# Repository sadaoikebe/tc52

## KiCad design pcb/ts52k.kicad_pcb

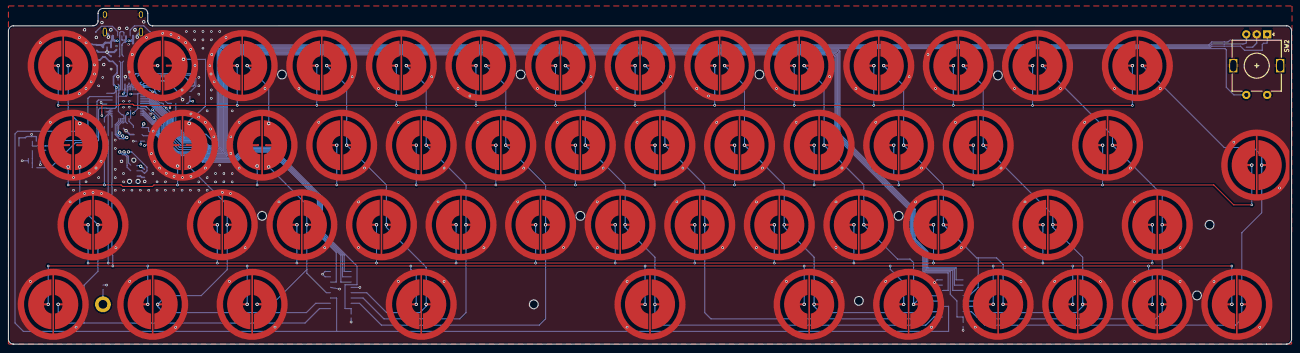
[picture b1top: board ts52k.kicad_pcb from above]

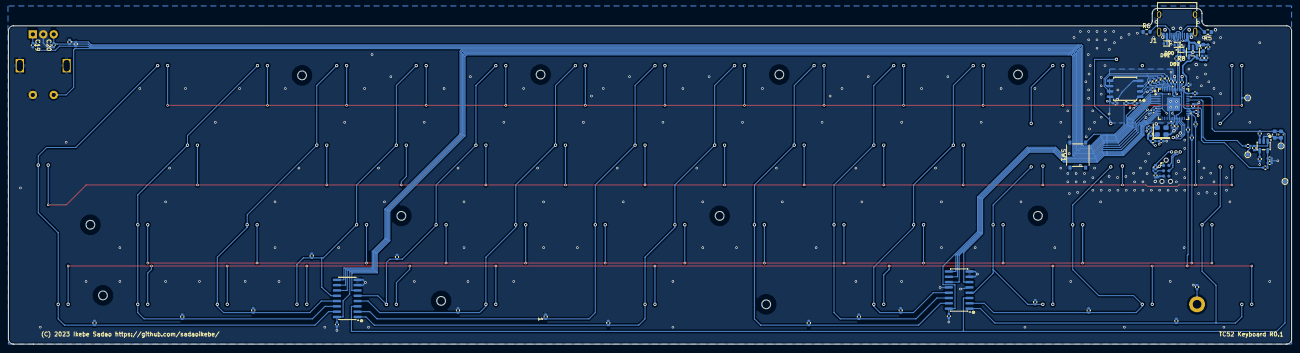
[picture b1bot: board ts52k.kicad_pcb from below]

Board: 4 copper layers, 307.2 x 80.4 mm, 148 parts (83 on the bottom side), 68 nets.

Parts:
C2, C4, C6, C7, C8, C9, C10, C12, C13, C14, C15, C16, C17, C18, C21: 1u; C_0402_1005Metric
C3: 4.7u; C_0603_1608Metric
C5, C32, C37: 4.7u; C_0402_1005Metric
C19, C20, C33, C34, C35: 0.1u; C_0402_1005Metric
C30: 300p C0G; C_0603_1608Metric
C31: DNP; C_0603_1608Metric
D89, D90, D91: H5VU10U; D_SOD-882D
H1: PLATE; Hole_M2_Pad
H2, H3, H4, H5, H6, H7, H8, H9, H10, H11, H12: M2; MountingHole_2.1mm
J1: HRO_TYPE-C-31-M-12; USB_C_Receptacle_HRO_TYPE-C-31-M-12
J2: TC2030_IDC_NL; Tag-Connect_TC2030-IDC-NL_2x03_P1.27mm_Vertical
MX2, MX3, MX4, MX5, MX7, MX8, MX9, MX11, MX12, MX13, MX14, MX16, MX17, MX18, MX20, MX21, MX22, MX23, MX25, MX26, MX27, MX29, MX30, MX31, MX33, MX34, MX35, MX37, MX38, MX39, MX42, MX43, MX44, MX46, MX47, MX48, MX51, MX52, MX55, MX56, MX58, MX60, MX61, MX64, MX65, MX66, MX67, MX71, MX75, MX81, MX82: ECS_PAD; ecs_pad
MX74: ECS_PAD; ecs_pad_edge
R2, R3, R4, R15, R16: 10k; R_0402_1005Metric
R5, R6: 5.1k; R_0603_1608Metric
R7, R8, R9, R10, R11, R12, R13, R24, R26: 22; R_0402_1005Metric
R14, R20: 1k; R_0402_1005Metric
R21: 43k 1%; R_0402_1005Metric
R22, R31, R32, R33, R34: 100; R_0402_1005Metric
R23: 0; R_0402_1005Metric
R25: DNP (0R); R_0402_1005Metric
R41, R42, R43, R44, R45, R46, R47, R48, R49, R50, R51, R52, R53, R54: 100k; R_0402_1005Metric
SW1: TS-1187A-B-A-B; SW_Tactile_XKB_TS-1187A_5.1x5.1mm
SW2: RotaryEncoder_Switch; RotaryEncoder_Alps_EC11E-Switch_Vertical_H20mm
TP1: SENSE; TestPoint_Pad_D1.0mm
TP2: ADC; TestPoint_Pad_D1.0mm
TP3: ROW1; TestPoint_Pad_D1.0mm
TP4: GND; TestPoint_Pad_D1.0mm
U3: TPS7A2433DBVR; SOT-23-5
U4: W25Q128JVS; SOIC-8_5.3x5.3mm_P1.27mm
U5: RP2040; IC57_RP2040
U6: AD8601ARTZ; SOT-23-5
U7, U8: CD4051BM96; SOIC-16_3.9x9.9mm_P1.27mm
X2: OC2EL89CJO-113YLC-12M; Oscillator_SMD_Abracon_ASE-4Pin_3.2x2.5mm

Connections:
+3V3: C2.2, C5.2, C6.1, C12.1, C13.1, C14.1, C15.1, C16.1, C17.1, C18.1, C21.1, J2.1, R2.1, R3.1, R4.1, R15.1, R16.1, R24.1, R26.1, U3.5, U4.8 (VCC), U5.1 (IOVDD), U5.10 (IOVDD), U5.22 (IOVDD), U5.33 (IOVDD), U5.42 (IOVDD), U5.43 (ADC_AVDD), U5.44 (VREG_VIN), U5.48 (USB_VDD), U5.49 (IOVDD), X2.4 (Vdd)
+3V3A: C32.1, C33.1, R24.2, U6.5
+3V3M: C34.1, C35.1, C37.1, R26.2, U7.16, U8.16
+5V: C3.2, C4.2, D91.1, J1.A4, J1.A9, J1.B4, J1.B9, U3.1, U3.3
/rp2040/1V1: C8.1, C9.1, C10.1, U5.23 (DVDD), U5.45 (VREG_VOUT), U5.50 (DVDD)
/rp2040/QSPI_SCLK: R9.1, U4.6 (CLK)
/rp2040/QSPI_SD0: R10.1, U4.5 (DI/IO_{0})
/rp2040/QSPI_SD1: R11.1, U4.2 (DO/IO_{1})
/rp2040/QSPI_SD2: R12.1, U4.3 (~WP/IO_{2})
/rp2040/QSPI_SD3: R13.1, U4.7 (~HOLD/~RESET/IO_{3})
ADC: R23.2, U5.38 (GPIO26/ADC0)
AMP_FB: R20.1, R21.2, U6.4
AMP_IN: R22.2, U6.3
AMP_OUT: R21.1, R23.1, TP2.1, U6.1
COL1: MX2.2, MX3.2, MX4.2, MX5.2, R41.1, U7.1
COL2: MX7.2, MX8.2, MX9.2, MX13.2, R42.1, U7.2
COL3: MX11.2, MX12.2, MX14.2, MX18.2, R43.1, U7.4
COL4: MX16.2, MX17.2, MX22.2, MX23.2, R44.1, U7.13
COL5: MX20.2, MX21.2, MX27.2, R45.1, U7.14
COL6: MX25.2, MX26.2, MX31.2, R46.1, U7.15
COL7: MX29.2, MX30.2, MX35.2, MX60.2, R47.1, U8.1
COL8: MX33.2, MX34.2, MX39.2, R48.1, U8.2
COL9: MX37.2, MX38.2, MX44.2, MX81.2, R49.1, U8.4
COL10: MX42.2, MX43.2, MX48.2, MX82.2, R50.1, U8.5
COL11: MX46.2, MX47.2, MX52.2, MX58.2, R51.1, U8.12
COL12: MX51.2, MX56.2, MX61.2, MX75.2, R52.1, U8.13
COL13: MX55.2, MX65.2, MX66.2, MX67.2, R53.1, U8.14
COL14: MX64.2, MX71.2, MX74.2, R54.1, U8.15
D+: D90.1, J1.A6, J1.B6, R8.1
D-: D89.1, J1.A7, J1.B7, R7.1
ENC_A: C19.1, R15.2, SW2.A, U5.3 (GPIO1)
ENC_B: C20.2, R16.2, SW2.B, U5.2 (GPIO0)
ENC_SW: SW2.S1, U5.4 (GPIO2)
GND: C2.1, C3.1, C4.1, C5.1, C6.2, C7.2, C8.2, C9.2, C10.2, C12.2, C13.2, C14.2, C15.2, C16.2, C17.2, C18.2, C19.2, C20.1, C21.2, C30.2, C31.2, C32.2, C33.2, C34.2, C35.2, C37.2, D89.2, D90.2, D91.2, J1.A1, J1.A12, J1.B1, J1.B12, J1.SH, J2.5, MX2.3, MX3.3, MX4.3, MX5.3, MX7.3, MX8.3, MX9.3, MX11.3, MX12.3, MX13.3, MX14.3, MX16.3, MX17.3, MX18.3, MX20.3, MX21.3, MX22.3, MX23.3, MX25.3, MX26.3, MX27.3, MX29.3, MX30.3, MX31.3, MX33.3, MX34.3, MX35.3, MX37.3, MX38.3, MX39.3, MX42.3, MX43.3, MX44.3, MX46.3, MX47.3, MX48.3, MX51.3, MX52.3, MX55.3, MX56.3, MX58.3, MX60.3, MX61.3, MX64.3, MX65.3, MX66.3, MX67.3, MX71.3, MX74.3, MX75.3, MX81.3, MX82.3, R5.1, R6.1, R20.2, R25.2, R41.2, R42.2, R43.2, R44.2, R45.2, R46.2, R47.2, R48.2, R49.2, R50.2, R51.2, R52.2, R53.2, R54.2, SW1.1, SW2.C, SW2.MP, SW2.S2, TP4.1, U3.2, U3.4, U4.4 (GND), U5.19 (TESTEN), U5.57 (EPAD), U6.2, U7.5, U7.7, U7.8, U7.12, U8.7, U8.8, X2.2 (GND)
INHA: U5.14 (GPIO11), U7.6
INHB: U5.9 (GPIO7), U8.6
unnamed: J1.A5, R5.2
unnamed: J1.B5, R6.2
unnamed: R14.2, SW1.2
unnamed: R9.2, U5.52 (QSPI_SCLK)
unnamed: R10.2, U5.53 (QSPI_SD0)
unnamed: R11.2, U5.55 (QSPI_SD1)
unnamed: R12.2, U5.54 (QSPI_SD2)
unnamed: R13.2, U5.51 (QSPI_SD3)
unnamed: R7.2, U5.46 (USB_DM)
unnamed: R8.2, U5.47 (USB_DP)
unnamed: U5.20 (XIN), X2.3 (OUT)
unnamed: R3.2, X2.1 (EN)
PLATE: H1.1, R25.1
QSPI_SS_N: R2.2, R14.1, U4.1 (~CS), U5.56 (QSPI_SS_N)
ROW1: MX2.1, MX7.1, MX11.1, MX16.1, MX20.1, MX25.1, MX29.1, MX33.1, MX37.1, MX42.1, MX46.1, MX51.1, MX55.1, MX64.1, R31.2, TP3.1
ROW1_DRV: R31.1, U5.32 (GPIO21)
ROW2: MX3.1, MX8.1, MX12.1, MX17.1, MX21.1, MX26.1, MX30.1, MX34.1, MX38.1, MX43.1, MX47.1, MX56.1, MX65.1, MX74.1, R32.2
ROW2_DRV: R32.1, U5.31 (GPIO20)
ROW3: MX4.1, MX13.1, MX18.1, MX22.1, MX27.1, MX31.1, MX35.1, MX39.1, MX44.1, MX48.1, MX52.1, MX66.1, MX75.1, R33.2
ROW3_DRV: R33.1, U5.30 (GPIO19)
ROW4: MX5.1, MX9.1, MX14.1, MX23.1, MX58.1, MX60.1, MX61.1, MX67.1, MX71.1, MX81.1, MX82.1, R34.2
ROW4_DRV: R34.1, U5.29 (GPIO18)
S1A: U5.13 (GPIO10), U7.11
S1B: U5.7 (GPIO5), U8.11
S2A: U5.12 (GPIO9), U7.10
S2B: U5.6 (GPIO4), U8.10
S3A: U5.11 (GPIO8), U7.9
S3B: U5.5 (GPIO3), U8.9
SENSE: C30.1, C31.1, R22.1, TP1.1, U5.40 (GPIO28/ADC2), U7.3, U8.3
SWCLK: J2.4, U5.24 (SWCLK)
SWDIO: J2.2, U5.25 (SWDIO)
~RST: C7.1, J2.3, R4.2, U5.26 (RUN)

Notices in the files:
pcb/ts52k.kicad_pcb:
(C) 2023 Ikebe Sadao https://github.com/sadaoikebe
